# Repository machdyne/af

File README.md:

# Machdyne AF

## Overview

Machdyne AF is an open-source project for a PNP autofeeder system[^1].

The autofeeder design is a closed-loop system that uses an infrared LED and phototransistor array[^2] to precisely detect the tape position. The tape is moved forward using a geared DC motor and a sprocket. The cover tape is partially separated and advanced with the tape.

The autofeeders can be chained together with 4 wires and communicate with the system controller using the I2C protocol.

The system uses two custom printed circuit board designs. An autofeeder controller PCB (Essen) includes the tape detection and motor driver circuitry for each autofeeder. A system controller PCB (Koch) provides power and allows a chain of feeders to communicate with the OpenPnP software over a USB-C port.

[^1]: This project is still under development and is not yet suitable for use in production.
[^2]: While the PCB has an array of six phototransistors, the firmware is currently using only one.

## Autofeeder 3D parts (AF1)

| Model | Image | Description |
| ----- | ----- | ----------- |
| [af](3d/stl/af.stl) |  | The autofeeder body guides the tape and holds the Essen PCB in place |
| [af_sprocket](3d/stl/af_sprocket.stl) |  | The sprocket advances the tape |
| [af_motor_lock](3d/stl/af_motor_lock.stl) |  | The motor lock holds the motor in place |
| [af_blade](3d/stl/af_blade.stl) |  | The blade partially peels the clear film from the top of the tape to the side |
| [af_led_block](3d/stl/af_led_block.stl) |  | The LED block holds the LED in place |
| [af_lid](3d/stl/af_lid.stl) |  | The lid closes the autofeeder and guides the tape |

### Bill of Materials

| Part | Quantity | Description | Example P/N |
| ---- | -------- | ----------- | ----------- |
| Worm gear motor | 1 | Right-angle N20 DC 12V 16 RPM | JGY-N20 |
| LED | 1 | 3mm 940nm 1.3Vf Infrared LED | DY-FIR204C |
| M3 bolt 12mm + nut | 1 | for blade | - |
| M3 screw 20mm countersunk | 1 | for LED block | - |
| M3 bolt 20mm countersunk + nut | 3 | for lid | - |
| M3 bolt 25mm | 1 | to connect LED block to rail |
| M3 T3 nut | 1 | to connect LED block to rail |

You will also need dupont jumper wires to connect the motor and LED to Essen.

### Assembly Instructions

Cut, strip and solder one end of the jumper wires to the motor leads and each lead of the LED. Press the LED into the LED block, and run the wires through the large LED block hole.

Attach the blade using an M3 bolt and nut.

Press the sprocket onto the motor axle. Press the motor into the motor cavity.

Run the LED wires through the rear autofeeder hole and connect to Essen LED\_A and LED\_K. Connect the motor wires to Essen MOT1 and MOT2.

Push the PCB onto the PCB notches so that it locks into place.

Attach the LED block using the screw.

Place the motor lock on top of the motor.

Attach the lid.

Connect Essen to Koch or other Essens using a 4-pin female-female 2.54mm dupont cable.

Attach the LED block to a 2020 rail with an M3 bolt and T-nut.

The assembled autofeeder (without lid):

## Autofeeder controller PCB (Essen)

Also see the [firmware and usage instructions](fw/essen).

### Pinout (Rear)

```
9  7  5  3  1
10 8  6  4  2
```

| Pin | Signal | Notes |
| --- | ------ | ----- |
| 9/10 | 12V | System power input |
| 7/8 | GND | Ground |
| 5/6 | SDA | I2C data |
| 3/4 | SCL | I2C clock |
| 2 | TRIGGER | Optional external tape advance signal |
| 1 | SWDIO | MCU SWD signal for firmware updates / serial debugging output |

### Pinout (Top)

| Pin | Signal | Notes |
| --- | ------ | ----- |
| 1 | MOT1 | Motor driver output #1 |
| 2 | GND | Ground |
| 3 | MOT2 | Motor driver output #2 |
| 4 | GND | Ground |
| 5 | ELED\_A | External (IR) LED anode |
| 6 | ELED\_K | External (IR) LED cathode |

The motor driver can drive one bidirectional motor or two unidirectional motors.

## System controller PCB (Koch)

Also see the [firmware and usage instructions](fw/koch).

### Pinout

```
1 2 3 4
```

| Pin | Signal | Notes |
| --- | ------ | ----- |
| 1 | 12V | System power output (2.5mm positive tip) |
| 2 | GND | System ground |
| 3 | SDA | I2C data |
| 4 | SCL | I2C clock |

## Funding

This project is being partially funded through the [NGI0 Entrust Fund](https://nlnet.nl/entrust/), a fund established by NLnet with financial support from the European Commission's Next Generation Internet programme.

## License

This project is released under the [CERN-OHL-P](LICENSE.txt) license.

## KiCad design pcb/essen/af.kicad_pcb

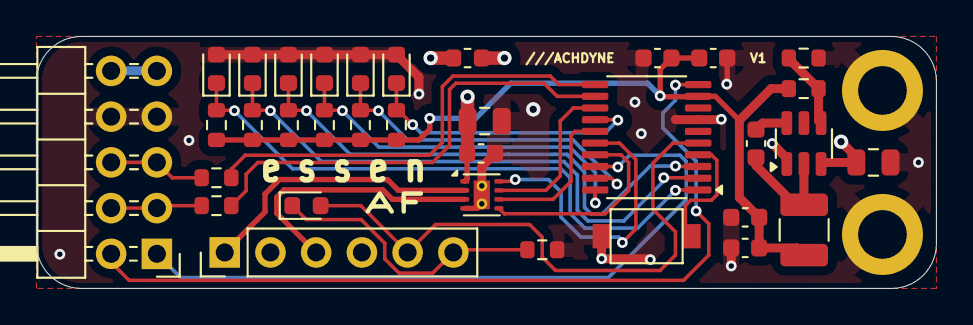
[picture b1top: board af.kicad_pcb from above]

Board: 2 copper layers, 50.0 x 14.0 mm, 36 parts (0 on the bottom side), 28 nets.

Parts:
C1: 100nF; C_0603_1608Metric
C2: 10uF; C_0603_1608Metric
C3: 22uF25v; C_0805_2012Metric
C6, C8: 100nF16v; C_0603_1608Metric
C7: 10uF16v; C_0805_2012Metric
C9, C10: 22uF; C_0603_1608Metric
D1: LED; LED_0603_1608Metric
F1: 500mA Hold 1A Trip 15V; Fuse_0603_1608Metric
H1, H2: MountingHole_Pad; MountingHole_2.7mm_M2.5_ISO14580_Pad
J1: Conn_02x05_Odd_Even; PinHeader_2x05_P2.54mm_Horizontal
J2: Conn_01x06_Pin; PinHeader_1x06_P2.54mm_Vertical
L1: 3.3uH 1.2A; L_1210_3225Metric
Q3, Q4, Q5, Q6, Q7, Q8: Q_Photo_NPN; D_0603_1608Metric
R1: 1K; R_0603_1608Metric
R2: 33K2; R_0603_1608Metric
R3, R4, R9, R10, R11, R12, R13: 10K; R_0603_1608Metric
R6, R7: 100R; R_0603_1608Metric
SW3: SW_Push; Button_2P_3x4mm
U1: CH32V003F4P6; TSSOP-20_4.4x6.5mm_P0.65mm
U3: DRV8220; WSON-8-1EP_2x2mm_P0.5mm_EP0.9x1.6mm_ThermalVias
U4: AP62300TWU-7; TSOT-23-6

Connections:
/A2: Q8.1 (C), R13.2, U1.14 (PC4)
/A3: Q7.1 (C), R12.2, U1.19 (PD2)
/A4: Q6.1 (C), R11.2, U1.20 (PD3)
/A5: Q4.1 (C), R9.2, U1.2 (PD5)
/A6: Q5.1 (C), R10.2, U1.3 (PD6)
/A7: Q3.1 (C), R4.2, U1.1 (PD4)
/DRV_IN1: U1.15 (PC5), U3.6 (IN1)
/DRV_IN2: U1.17 (PC7), U3.5 (IN2)
/DRV_MODE: U1.13 (PC3), U3.7 (MODE)
/DRV_SLP: U1.16 (PC6), U3.8 (SLEEP_N)
/ELED_A: D1.2 (A), J2.5, U1.5 (PA1)
/ELED_K: D1.1 (K), J2.6, R1.2
/MOT1: J2.1, U3.2 (OUT1)
/MOT2: J2.3, U3.3 (OUT2)
/PWR3V3: C1.1, C2.1, C9.1, C10.1, L1.2, R2.2, R4.1, R9.1, R10.1, R11.1, R12.1, R13.1, U1.9 (VDD)
/PWRIN: C3.1, C6.1, C7.1, F1.2, U3.1 (VM), U4.3 (VIN)
/PWRINC: F1.1, J1.9, J1.10
/RESET: SW3.1, U1.4 (PD7)
/SCL: R7.2, U1.12 (PC2)
/SCLC: J1.3, J1.4, R7.1
/SDA: R6.2, U1.11 (PC1)
/SDAC: J1.5, J1.6, R6.1
/SW: C8.2, L1.1, U4.2 (SW)
/SWDIO: J1.1, U1.18 (PD1)
/TRIGGER: J1.2, U1.10 (PC0)
GND: C1.2, C2.2, C3.2, C6.2, C7.2, C9.2, C10.2, H1.1, H2.1, J1.7, J1.8, J2.2, J2.4, Q3.2 (E), Q4.2 (E), Q5.2 (E), Q6.2 (E), Q7.2 (E), Q8.2 (E), R1.1, R3.1, SW3.2, U1.7 (VSS), U3.4 (GND), U3.9 (EP), U4.1 (GND)
unnamed: C8.1, U4.6 (BST)
unnamed: R2.1, R3.2, U4.4 (FB)

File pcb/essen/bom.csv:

"Id";"Designator";"Footprint";"Quantity";"Designation";"Supplier and ref";
1;"R13,R9,R3,R10,R11,R12,R4";"R_0603_1608Metric";7;"10K";;;
2;"H1,H2";"MountingHole_2.7mm_M2.5_ISO14580_Pad";2;"MountingHole_Pad";;;
3;"L1";"L_1210_3225Metric";1;"3.3uH 1.2A";;;
4;"U3";"WSON-8-1EP_2x2mm_P0.5mm_EP0.9x1.6mm_ThermalVias";1;"DRV8220";;;
5;"C9,C10";"C_0603_1608Metric";2;"22uF";;;
6;"Q7,Q6,Q4,Q8,Q5,Q3";"D_0603_1608Metric";6;"Q_Photo_NPN";"XL-1608PDC";;
7;"C8,C6";"C_0603_1608Metric";2;"100nF16v";;;
8;"U1";"TSSOP-20_4.4x6.5mm_P0.65mm";1;"CH32V003F4P6";;;
9;"C3";"C_0805_2012Metric";1;"22uF25v";;;
10;"J2";"PinHeader_1x06_P2.54mm_Vertical";1;"Conn_01x06_Pin";;;
11;"C1";"C_0603_1608Metric";1;"100nF";;;
12;"SW3";"Button_2P_3x4mm";1;"SW_Push";;;
13;"R1";"R_0603_1608Metric";1;"1K";;;
14;"F1";"Fuse_0603_1608Metric";1;"500mA Hold 1A Trip 15V";;;
15;"C7";"C_0805_2012Metric";1;"10uF16v";;;
16;"R6,R7";"R_0603_1608Metric";2;"100R";;;
17;"D1";"LED_0603_1608Metric";1;"LED";;;
18;"U4";"TSOT-23-6";1;"AP62300TWU-7";;;
19;"C2";"C_0603_1608Metric";1;"10uF";;;
20;"R2";"R_0603_1608Metric";1;"33K2";;;
21;"J1";"PinHeader_2x05_P2.54mm_Horizontal";1;"Conn_02x05_Odd_Even";;;
22;"G***";"ld-kicad";1;"LOGO";;;

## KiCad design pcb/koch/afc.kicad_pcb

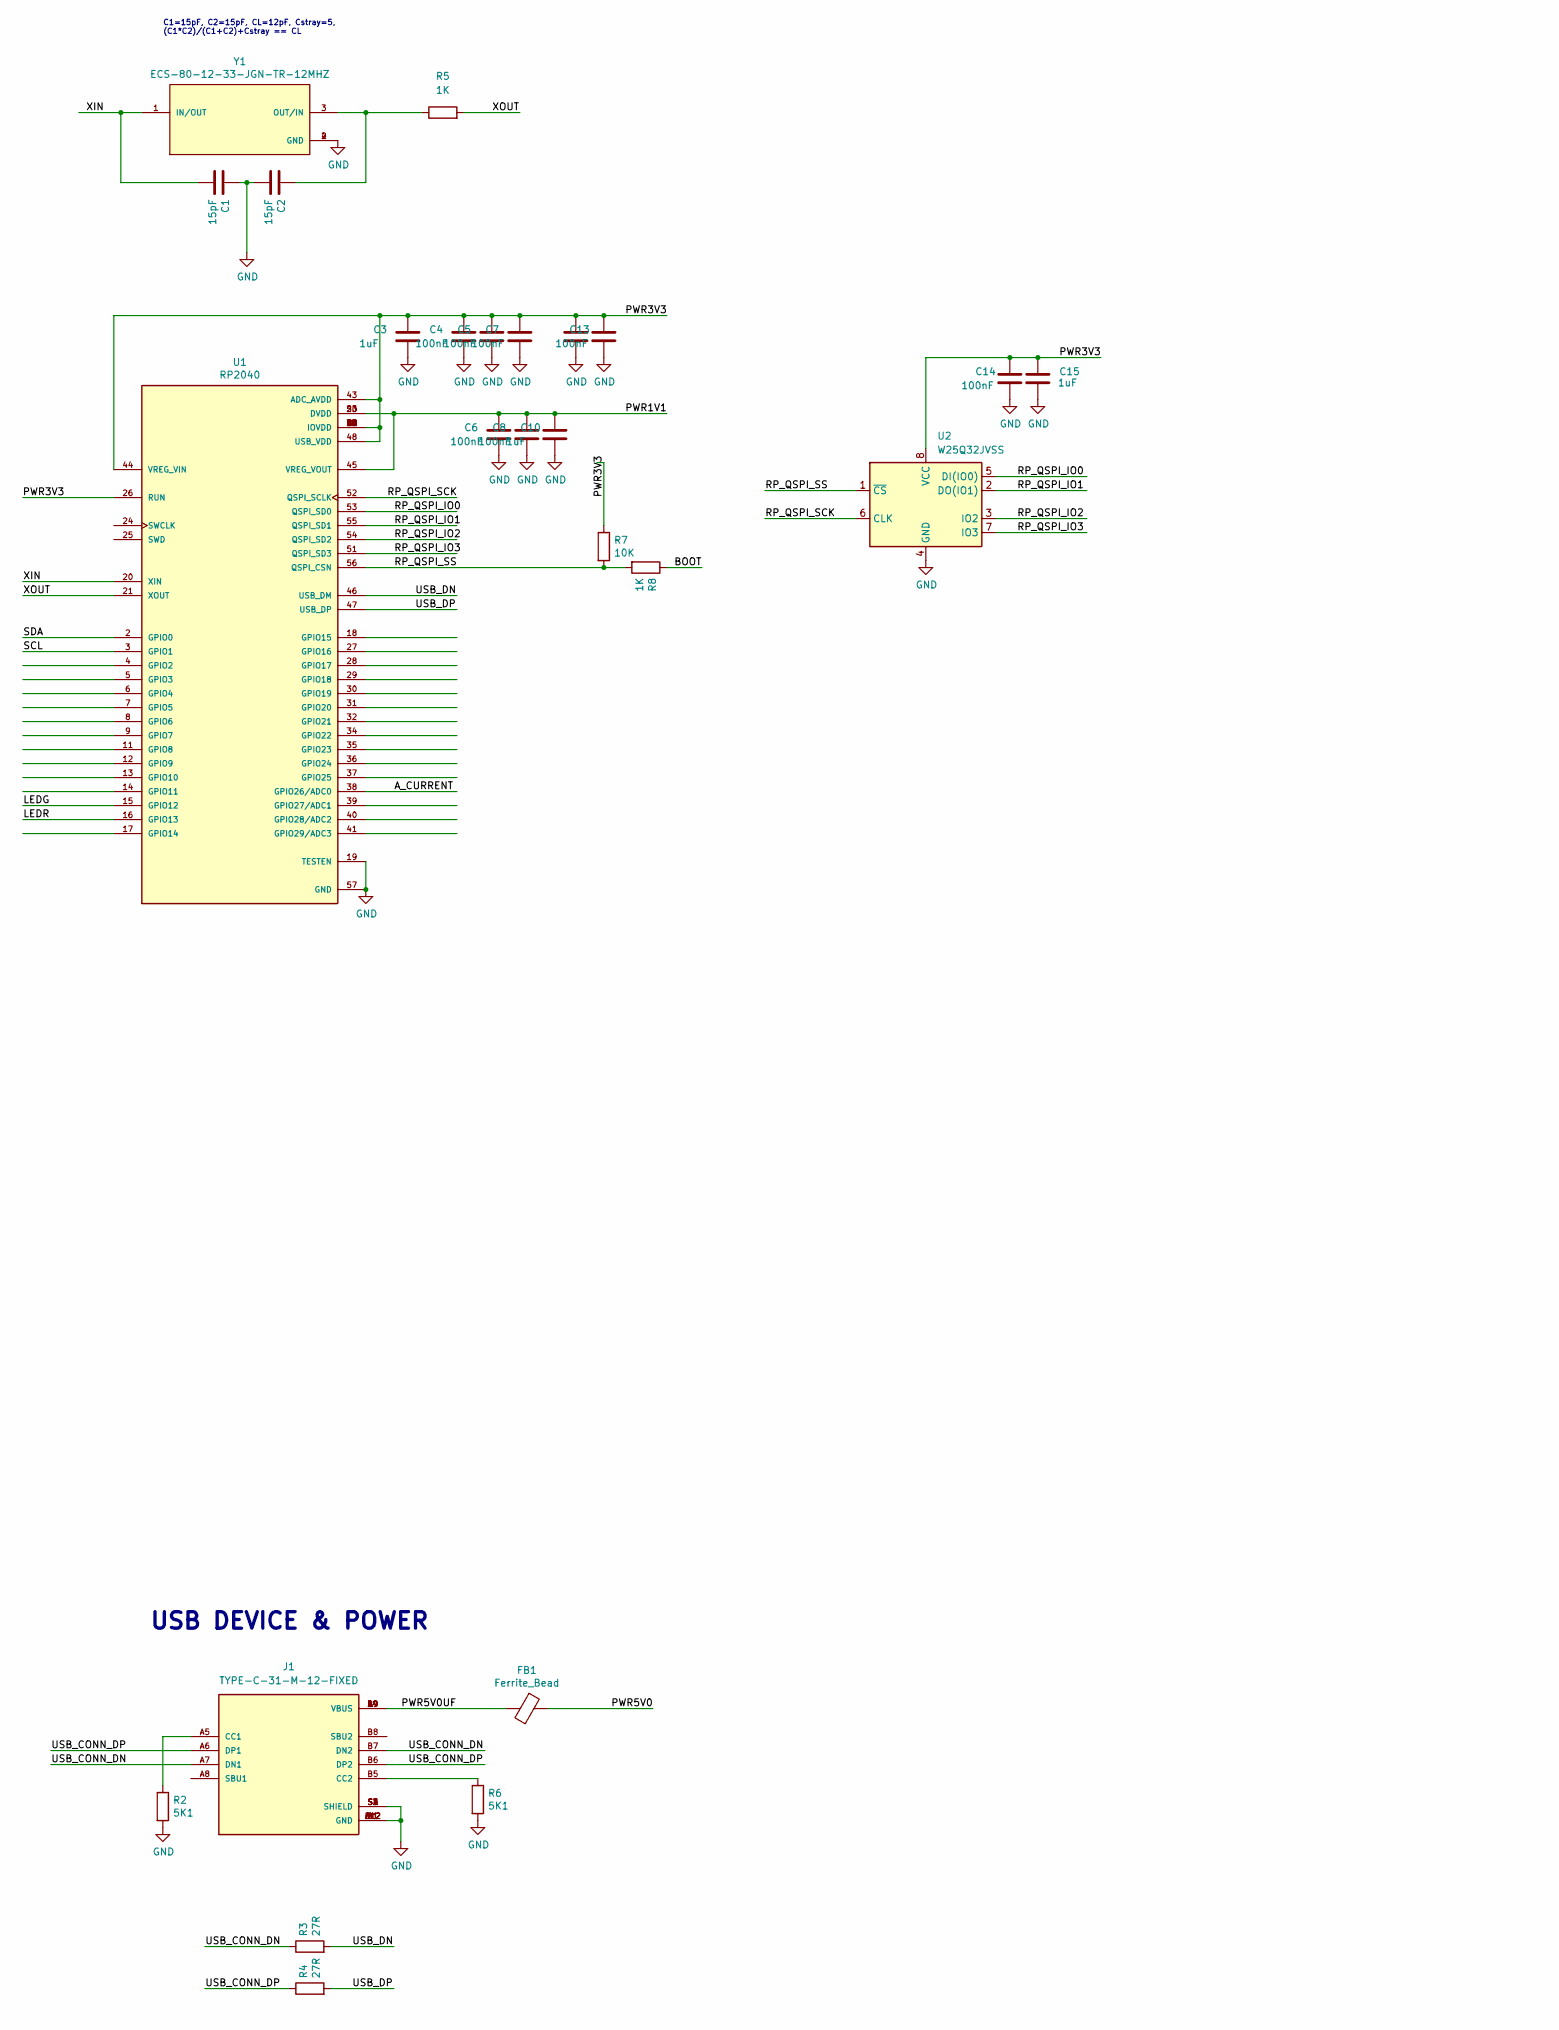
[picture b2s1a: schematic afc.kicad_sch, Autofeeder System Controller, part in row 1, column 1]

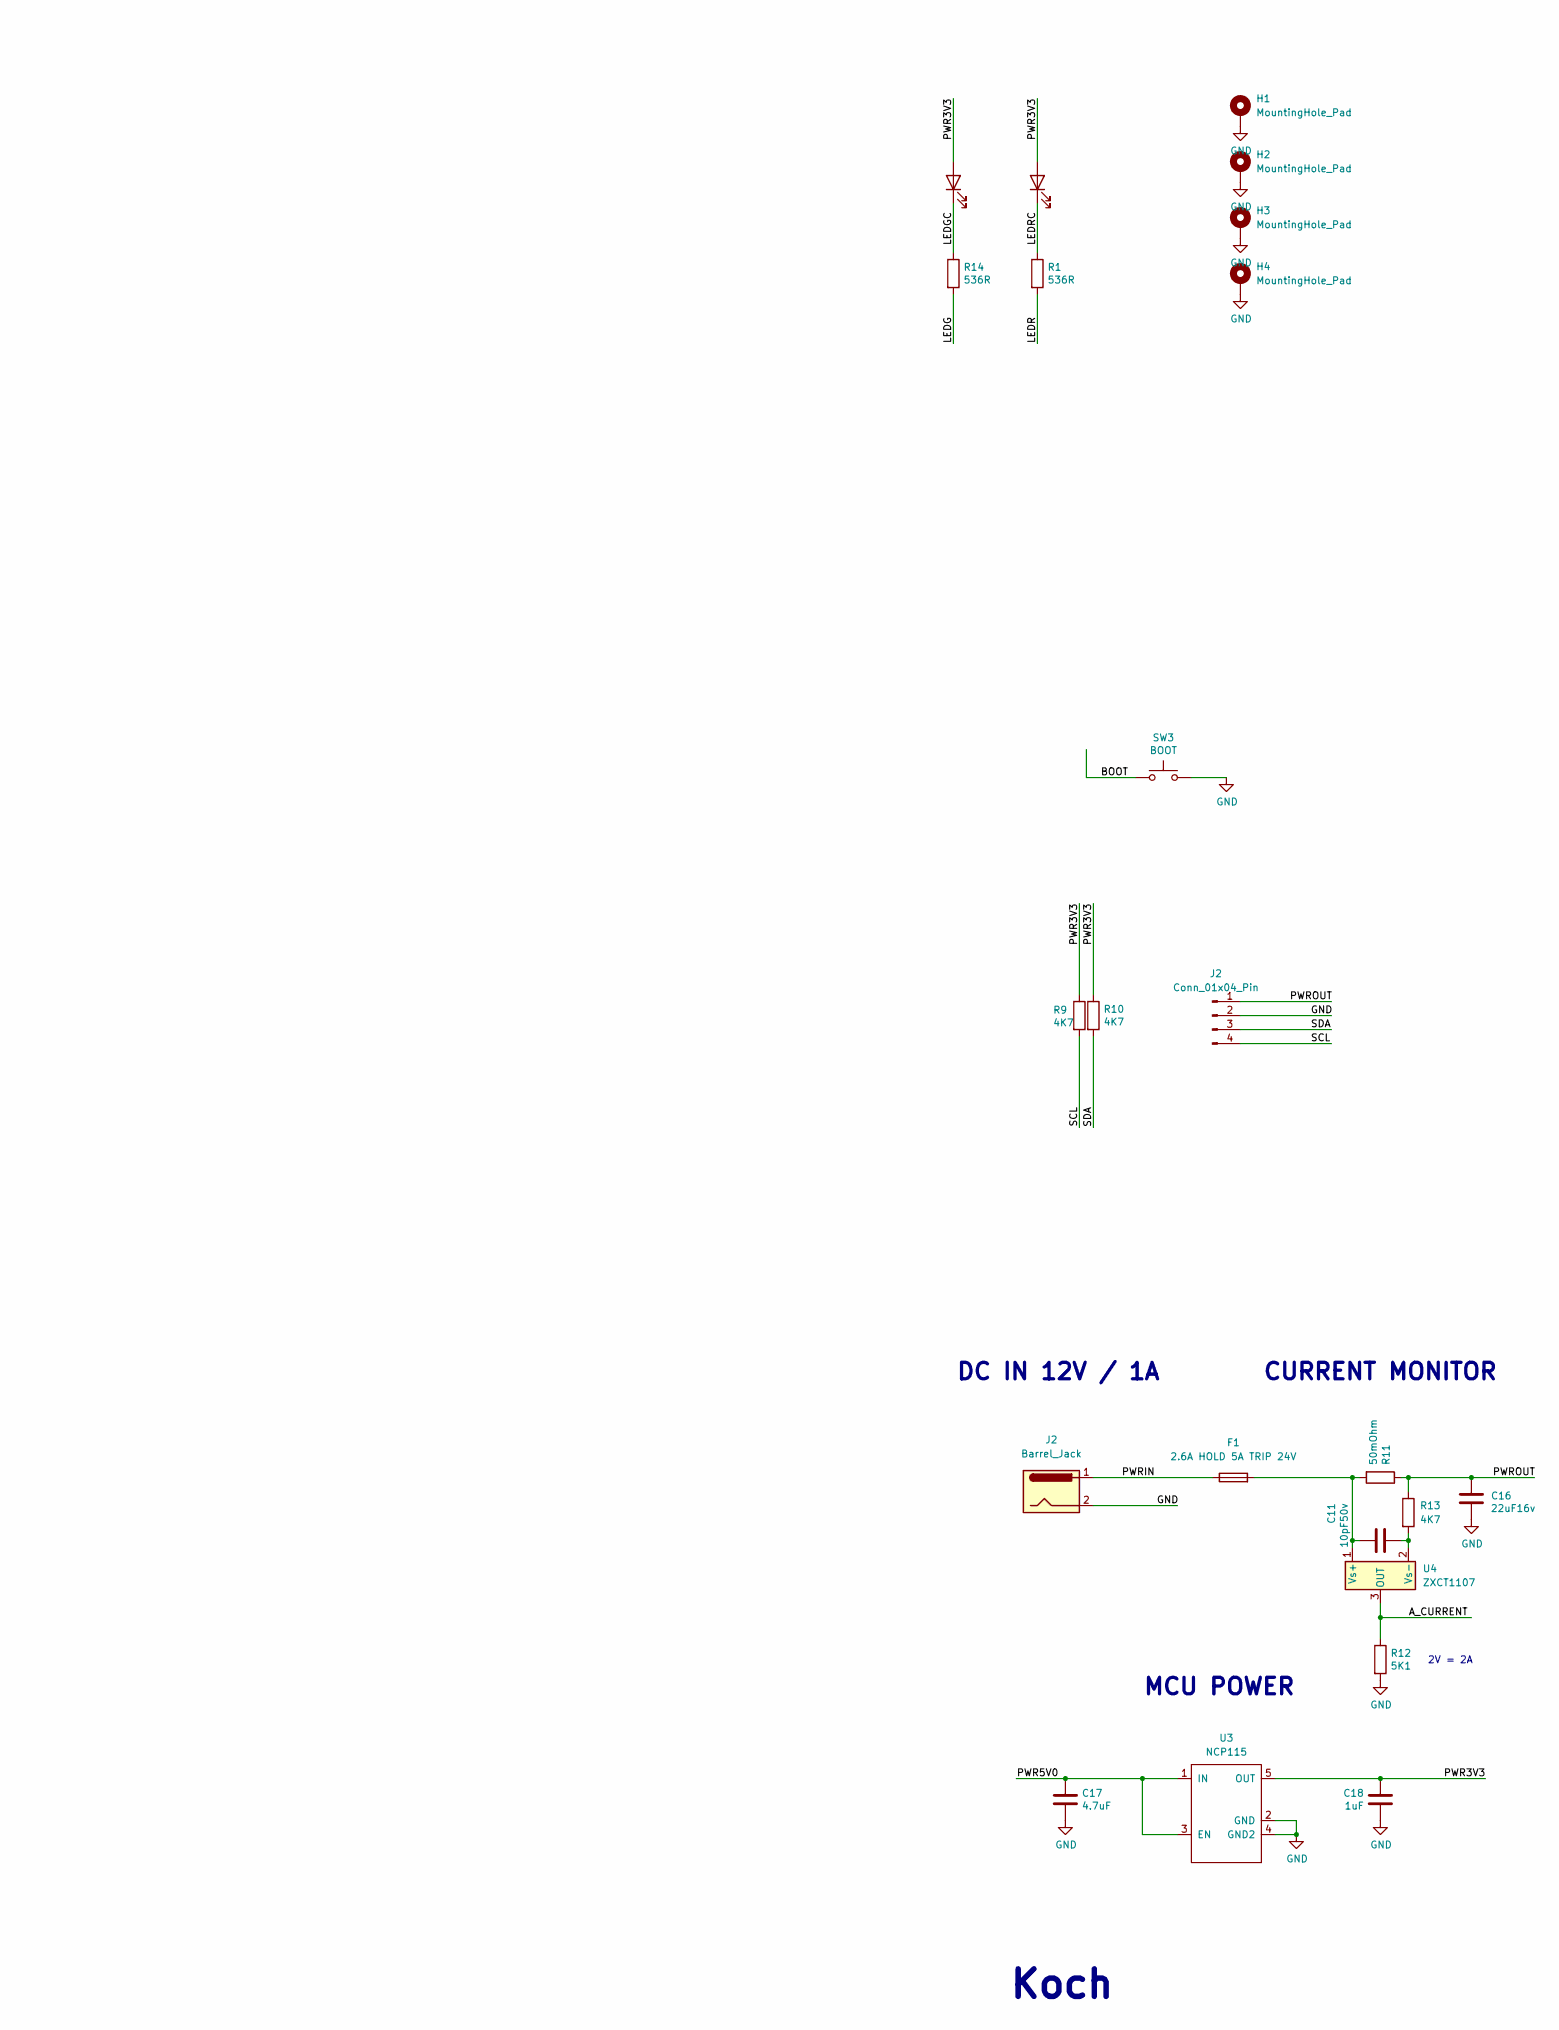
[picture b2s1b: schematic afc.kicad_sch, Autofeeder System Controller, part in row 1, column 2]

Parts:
C1, C2: 15pF; C_0603_1608Metric
C3, C10, C15, C18: 1uF; C_0603_1608Metric
C4, C5, C6, C7, C8, C12, C13, C14: 100nF; C_0603_1608Metric
C11: 10pF50v; C_0603_1608Metric
C16: 22uF16v; C_0805_2012Metric
C17: 4.7uF; C_0603_1608Metric
D1: LEDG; LED_0603_1608Metric
D2: LEDR; LED_0603_1608Metric
F1: 2.6A HOLD 5A TRIP 24V; Fuse_1210_3225Metric
FB1: Ferrite_Bead; R_0603_1608Metric
H1, H2, H3, H4: MountingHole_Pad; MountingHole_3.2mm_M3_ISO14580_Pad
J1: TYPE-C-31-M-12-FIXED; USB_C_Receptacle_HRO_TYPE-C-31-M-12-BIG-PADS; PARTREV A
J2: Barrel_Jack; BarrelJack_GCT_DCJ200-10-A_Horizontal
R1, R14: 536R; R_0603_1608Metric
R2, R6, R12: 5K1; R_0603_1608Metric
R3, R4: 27R; R_0603_1608Metric
R5, R8: 1K; R_0603_1608Metric
R7: 10K; R_0603_1608Metric
R9, R10: 4K7; R_0603_1608Metric
R11: 50mOhm; R_1206_3216Metric
R13: 4K7; R_1206_3216Metric
SW3: BOOT; SW_Tactile_SPST_Angled_PTS645Vx39-2LFS
U1: RP2040; RP2040-QFN-56-OFFICIAL; PARTREV 1.6.1
U2: W25Q32JVSS; SOIC-8_3.9x4.9mm_P1.27mm
U3: NCP115; TSOP-5_1.65x3.05mm_P0.95mm
U4: ZXCT1107; SOT-23
Y1: ECS-80-12-33-JGN-TR-12MHZ; XTAL_ECS-240-8-33-AGN-TR

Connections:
/A_CURRENT: R12.1, U1.38 (GPIO26/ADC0), U4.3 (OUT)
/BOOT: R8.1, SW3.1
/LEDG: R14.2, U1.15 (GPIO12)
/LEDGC: D1.1 (K), R14.1
/LEDR: R1.2, U1.16 (GPIO13)
/LEDRC: D2.1 (K), R1.1
/PWR1V1: C6.1, C8.1, C10.1, U1.23 (DVDD), U1.45 (VREG_VOUT), U1.50 (DVDD)
/PWR3V3: C3.1, C4.1, C5.1, C7.1, C12.1, C13.1, C14.1, C15.1, C18.1, D1.2 (A), D2.2 (A), R7.1, R9.1, R10.1, U1.1 (IOVDD), U1.10 (IOVDD), U1.22 (IOVDD), U1.26 (RUN), U1.33 (IOVDD), U1.42 (IOVDD), U1.43 (ADC_AVDD), U1.44 (VREG_VIN), U1.48 (USB_VDD), U1.49 (IOVDD), U2.8 (VCC), U3.5 (OUT)
/PWR5V0: C17.1, FB1.1, U3.1 (IN), U3.3 (EN)
/PWR5V0UF: FB1.2, J1.A4 (VBUS), J1.A9 (VBUS), J1.B4 (VBUS), J1.B9 (VBUS)
/RP_QSPI_IO0: U1.53 (QSPI_SD0), U2.5 (DI(IO0))
/RP_QSPI_IO1: U1.55 (QSPI_SD1), U2.2 (DO(IO1))
/RP_QSPI_IO2: U1.54 (QSPI_SD2), U2.3 (IO2)
/RP_QSPI_IO3: U1.51 (QSPI_SD3), U2.7 (IO3)
/RP_QSPI_SCK: U1.52 (QSPI_SCLK), U2.6 (CLK)
/RP_QSPI_SS: R7.2, R8.2, U1.56 (QSPI_CSN), U2.1 (~CS)
/SCL: J2.4, R9.2, U1.3 (GPIO1)
/SDA: J2.3, R10.2, U1.2 (GPIO0)
/USB_CONN_DN: J1.A7 (DN1), J1.B7 (DN2), R3.1
/USB_CONN_DP: J1.A6 (DP1), J1.B6 (DP2), R4.1
/USB_DN: R3.2, U1.46 (USB_DM)
/USB_DP: R4.2, U1.47 (USB_DP)
/XIN: C1.2, U1.20 (XIN), Y1.1 (IN/OUT)
/XOUT: R5.2, U1.21 (XOUT)
GND: C1.1, C2.2, C3.2, C4.2, C5.2, C6.2, C7.2, C8.2, C10.2, C12.2, C13.2, C14.2, C15.2, C16.2, C17.2, C18.2, H1.1, H2.1, H3.1, H4.1, J1.A1 (GND), J1.A12 (GND), J1.B1 (GND), J1.B12 (GND), J1.S1 (SHIELD), J1.S2 (SHIELD), J1.S3 (SHIELD), J1.S4 (SHIELD), J2.2, R2.2, R6.2, R12.2, SW3.2, U1.19 (TESTEN), U1.57 (GND), U2.4 (GND), U3.2 (GND), U3.4 (GND2), Y1.2 (GND), Y1.4 (GND); also elsewhere on the board
unnamed: J1.A5 (CC1), R2.1
unnamed: J1.B5 (CC2), R6.1
unnamed: C11.1, F1.2, R11.2, U4.1 (Vs+)
unnamed: C11.2, R13.2, U4.2 (Vs-)
unnamed: C2.1, R5.1, Y1.3 (OUT/IN)

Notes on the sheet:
MCU POWER
C1=15pF, C2=15pF, CL=12pF, Cstray=5, (C1*C2)/(C1+C2)+Cstray == CL
Koch
USB DEVICE & POWER
2V = 2A
CURRENT MONITOR
DC IN 12V / 1A

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
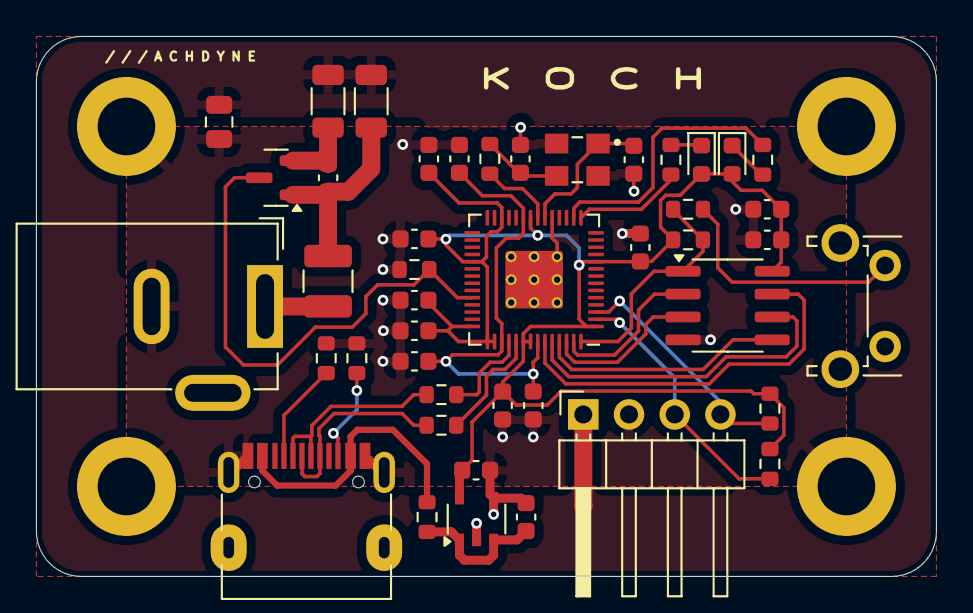
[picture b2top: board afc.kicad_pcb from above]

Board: 2 copper layers, 50.0 x 30.0 mm, 48 parts (0 on the bottom side), 32 nets.

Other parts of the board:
J3: Barrel_Jack; BarrelJack_GCT_DCJ200-10-A_Horizontal

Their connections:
GND: J3.2; also elsewhere on the board

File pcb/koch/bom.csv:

"Id";"Designator";"Footprint";"Quantity";"Designation";"Supplier and ref";
1;"C6,C5,C8,C14,C12,C4,C13,C7";"C_0603_1608Metric";8;"100nF";;;
2;"C2,C1";"C_0603_1608Metric";2;"15pF";;;
3;"R12,R2,R6";"R_0603_1608Metric";3;"5K1";;;
4;"R7";"R_0603_1608Metric";1;"10K";;;
5;"C3,C18,C15,C10";"C_0603_1608Metric";4;"1uF";;;
6;"J3";"BarrelJack_GCT_DCJ200-10-A_Horizontal";1;"Barrel_Jack";;;
7;"D2";"LED_0603_1608Metric";1;"LEDR";;;
8;"R13";"R_1206_3216Metric";1;"4K7";;;
9;"R4,R3";"R_0603_1608Metric";2;"27R";;;
10;"H1,H4,H2,H3";"MountingHole_3.2mm_M3_ISO14580_Pad";4;"MountingHole_Pad";;;
11;"R1,R14";"R_0603_1608Metric";2;"536R";;;
12;"U2";"SOIC-8_3.9x4.9mm_P1.27mm";1;"W25Q32JVSS";;;
13;"J2";"PinHeader_1x04_P2.54mm_Horizontal";1;"Conn_01x04_Pin";;;
14;"F1";"Fuse_1210_3225Metric";1;"2.6A HOLD 5A TRIP 24V";;;
15;"U4";"SOT-23";1;"ZXCT1107";;;
16;"U3";"TSOP-5_1.65x3.05mm_P0.95mm";1;"NCP115";;;
17;"D1";"LED_0603_1608Metric";1;"LEDG";;;
18;"C11";"C_0603_1608Metric";1;"10pF50v";;;
19;"C17";"C_0603_1608Metric";1;"4.7uF";;;
20;"U1";"RP2040-QFN-56-OFFICIAL";1;"RP2040";;;
21;"J1";"USB_C_Receptacle_HRO_TYPE-C-31-M-12-BIG-PADS";1;"TYPE-C-31-M-12-FIXED";;;
22;"R8,R5";"R_0603_1608Metric";2;"1K";;;
23;"SW3";"SW_Tactile_SPST_Angled_PTS645Vx39-2LFS";1;"BOOT";;;
24;"C16";"C_0805_2012Metric";1;"22uF16v";;;
25;"R9,R10";"R_0603_1608Metric";2;"4K7";;;
26;"R11";"R_1206_3216Metric";1;"50mOhm";;;
27;"FB1";"R_0603_1608Metric";1;"Ferrite_Bead";;;
28;"Y1";"XTAL_ECS-240-8-33-AGN-TR";1;"ECS-80-12-33-JGN-TR-12MHZ";;;

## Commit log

2024-09-19 update hardware notes
2024-12-02 add 3d parts
2024-12-02 add missing part

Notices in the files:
pcb/koch/afc.kicad_sch:
Copyright © 2024 Lone Dynamics Corporation
